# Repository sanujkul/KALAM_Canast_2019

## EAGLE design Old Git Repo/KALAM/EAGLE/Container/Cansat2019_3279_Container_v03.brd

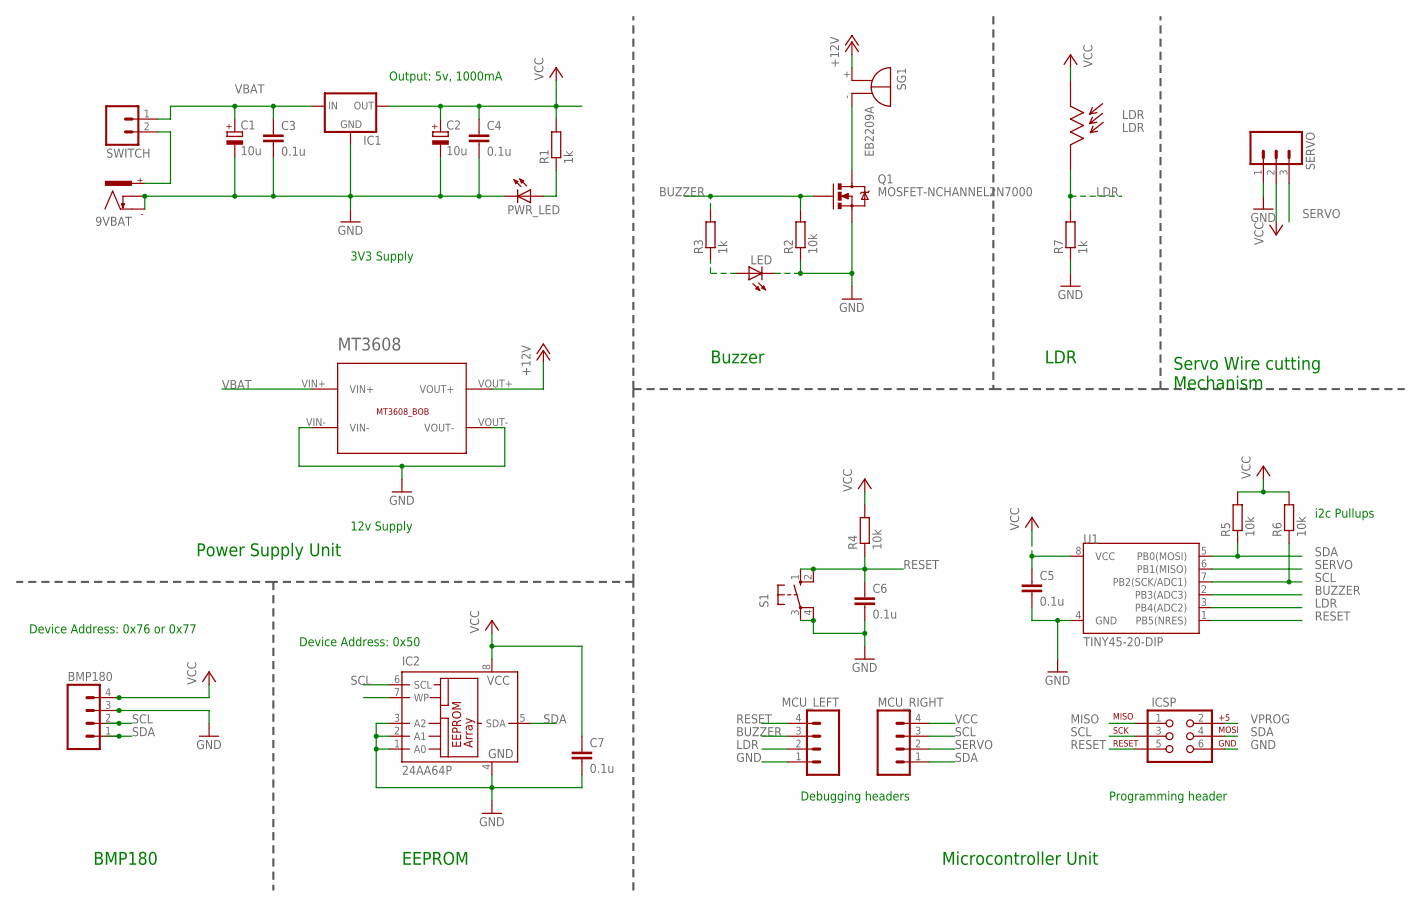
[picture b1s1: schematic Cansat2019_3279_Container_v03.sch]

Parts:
9VBAT: POWER_CON; NEB21R
BMP180: M04; 04P
C1, C2: 10u; E2,5-6
C3, C4, C5, C6, C7: 0.1u; C025-025X050
IC1: V_REG_78XX-TO-220; TO-220-ALT
IC2: 24AA64P; DIL8
ICSP: AVR_SPI_PRG_6NS; 2X3-NS
LDR: LDR; LDR-5MM
LED: LED3MM
MCU_LEFT: M04; 04P
MCU_RIGHT: M04; 04P
MT3608: MT3608_BOB
PWR_LED: LED3MM
Q1: MOSFET-NCHANNEL2N7000; TO-92
R1, R3, R7: 1k; 0204/7
R2, R4, R5, R6: 10k; 0204/7
S1: PUSH-BUTTON-6MM; B3F-10XX
SERVO: M03; 03P
SG1: EB2209A
SWITCH: M02; 02P
U1: TINY45-20-DIP; DIP08

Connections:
+12V: MT3608.VOUT+, SG1.+
BUZZER: MCU_LEFT.3, Q1.2 (G), R2.2, R3.2, U1.2 (PB3(ADC3))
GND: 9VBAT.-, 9VBAT.C, BMP180.3, C1.-, C2.-, C3.2, C4.2, C5.2, C6.2, C7.2, IC1.GND, IC2.1 (A0), IC2.2 (A1), IC2.3 (A2), IC2.4 (GND), ICSP.6, LED.K (C), MCU_LEFT.1, MT3608.VIN-, MT3608.VOUT-, PWR_LED.K (C), Q1.1 (S), R2.1, R7.1, S1.3, S1.4 (P1), SERVO.1, U1.4 (GND)
LDR: LDR.P$2, MCU_LEFT.2, R7.2, U1.3 (PB4(ADC2))
MISO: ICSP.1
unnamed: Q1.3 (D), SG1.-
unnamed: LED.A, R3.1
unnamed: PWR_LED.A, R1.1
unnamed: 9VBAT.+, SWITCH.2
RESET: C6.1, ICSP.5, MCU_LEFT.4, R4.1, S1.1 (S), S1.2 (S1), U1.1 (PB5(NRES))
SCL: BMP180.2, IC2.6 (SCL), ICSP.3, MCU_RIGHT.3, R6.1, U1.7 (PB2(SCK/ADC1))
SDA: BMP180.1, IC2.5 (SDA), ICSP.4, MCU_RIGHT.1, R5.1, U1.5 (PB0(MOSI))
SERVO: MCU_RIGHT.2, SERVO.3, U1.6 (PB1(MISO))
VBAT: C1.+, C3.1, IC1.IN, MT3608.VIN+, SWITCH.1
VCC: BMP180.4, C2.+, C4.1, C5.1, C7.1, IC1.OUT, IC2.8 (VCC), LDR.P$1, MCU_RIGHT.4, R1.2, R4.2, R5.2, R6.2, SERVO.2, U1.8 (VCC)
VPROG: ICSP.2

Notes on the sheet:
Power Supply Unit
Buzzer
Servo Wire cutting Mechanism
Debugging headers
Programming header
Microcontroller Unit
3V3 Supply
12v Supply
BMP180
i2c Pullups
Output: 5v, 1000mA
Device Address: 0x50
EEPROM
Device Address: 0x76 or 0x77
LDR

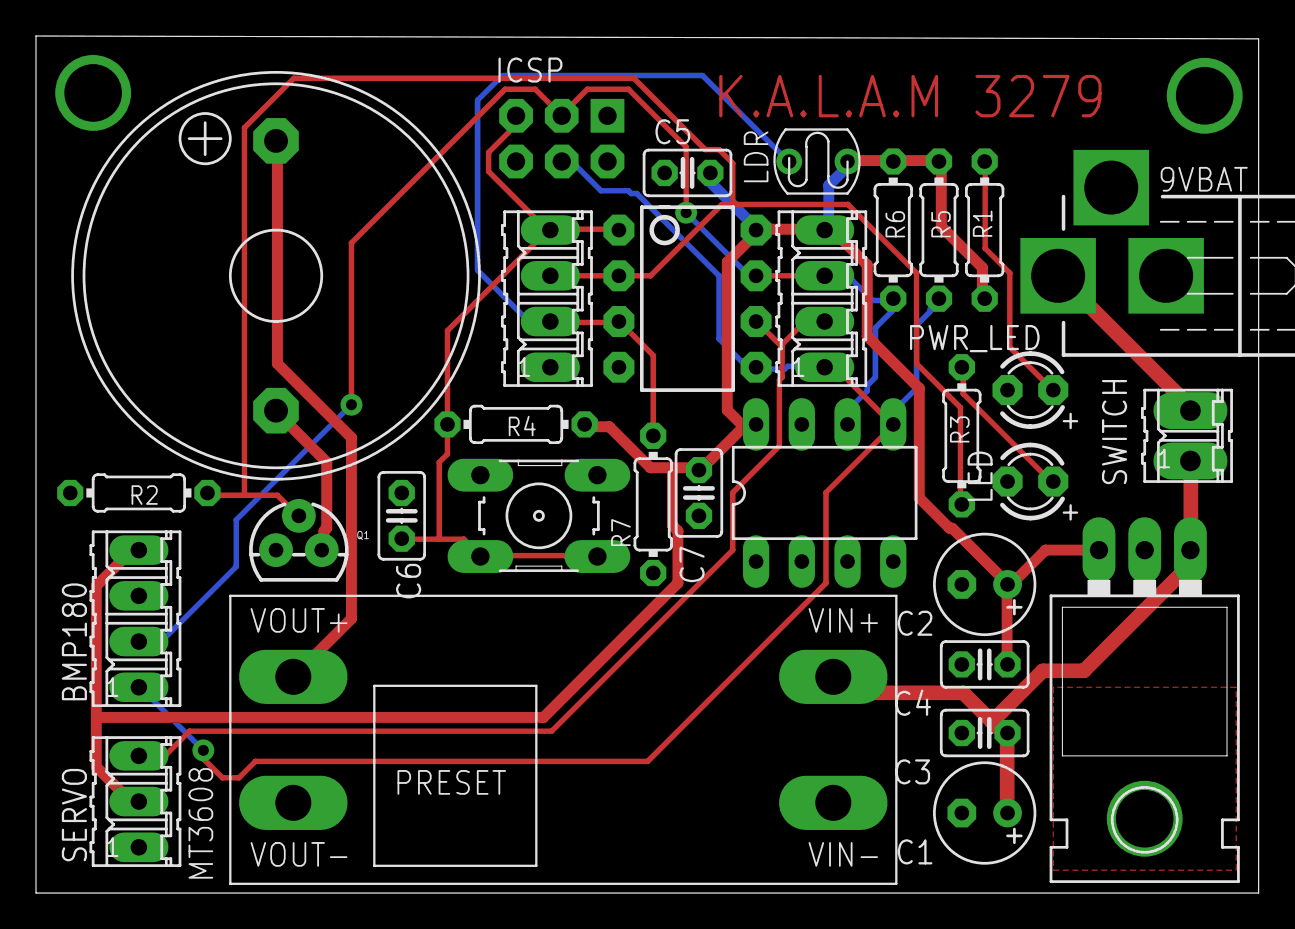
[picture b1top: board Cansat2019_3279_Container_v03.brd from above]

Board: 2 copper layers, 67.9 x 47.6 mm, 31 parts (0 on the bottom side), 14 nets.

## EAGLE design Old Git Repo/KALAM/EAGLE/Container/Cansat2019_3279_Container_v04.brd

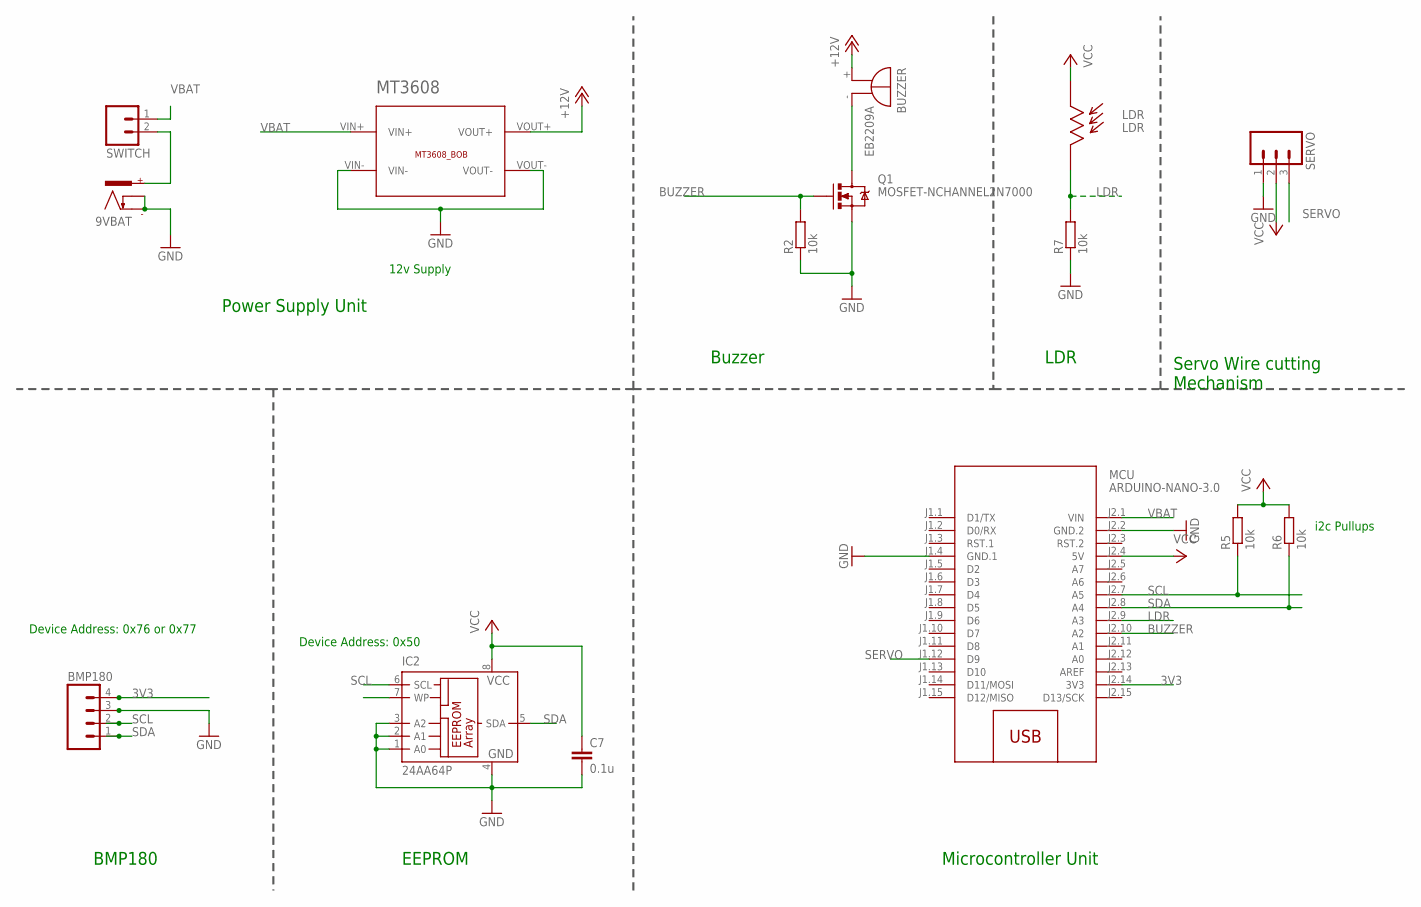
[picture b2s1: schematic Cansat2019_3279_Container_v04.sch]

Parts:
9VBAT: POWER_CON; NEB21R
BMP180: M04; 04P
BUZZER: EB2209A
C7: 0.1u; C025-025X050
IC2: 24AA64P; DIL8
LDR: LDR; LDR-5MM
MCU: ARDUINO-NANO-3.0
MT3608: MT3608_BOB
Q1: MOSFET-NCHANNEL2N7000; TO-92
R2, R5, R6, R7: 10k; 0204/7
SERVO: M03; 03P
SWITCH: M02; 02P

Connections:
3V3: BMP180.4, MCU.J2.14 (3V3)
+12V: BUZZER.+, MT3608.VOUT+
BUZZER: MCU.J2.10 (A2), Q1.2 (G), R2.2
GND: 9VBAT.-, 9VBAT.C, BMP180.3, C7.2, IC2.1 (A0), IC2.2 (A1), IC2.3 (A2), IC2.4 (GND), MCU.J1.4 (GND.1), MCU.J2.2 (GND.2), MT3608.VIN-, MT3608.VOUT-, Q1.1 (S), R2.1, R7.1, SERVO.1
LDR: LDR.P$2, MCU.J2.9 (A3), R7.2
unnamed: BUZZER.-, Q1.3 (D)
unnamed: 9VBAT.+, SWITCH.2
SCL: BMP180.2, IC2.6 (SCL), MCU.J2.7 (A5), R5.1
SDA: BMP180.1, IC2.5 (SDA), MCU.J2.8 (A4), R6.1
SERVO: MCU.J1.12 (D9), SERVO.3
VBAT: MCU.J2.1 (VIN), MT3608.VIN+, SWITCH.1
VCC: C7.1, IC2.8 (VCC), LDR.P$1, MCU.J2.4 (5V), R5.2, R6.2, SERVO.2

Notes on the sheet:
Power Supply Unit
Buzzer
Servo Wire cutting Mechanism
Microcontroller Unit
12v Supply
BMP180
i2c Pullups
Device Address: 0x50
EEPROM
Device Address: 0x76 or 0x77
LDR

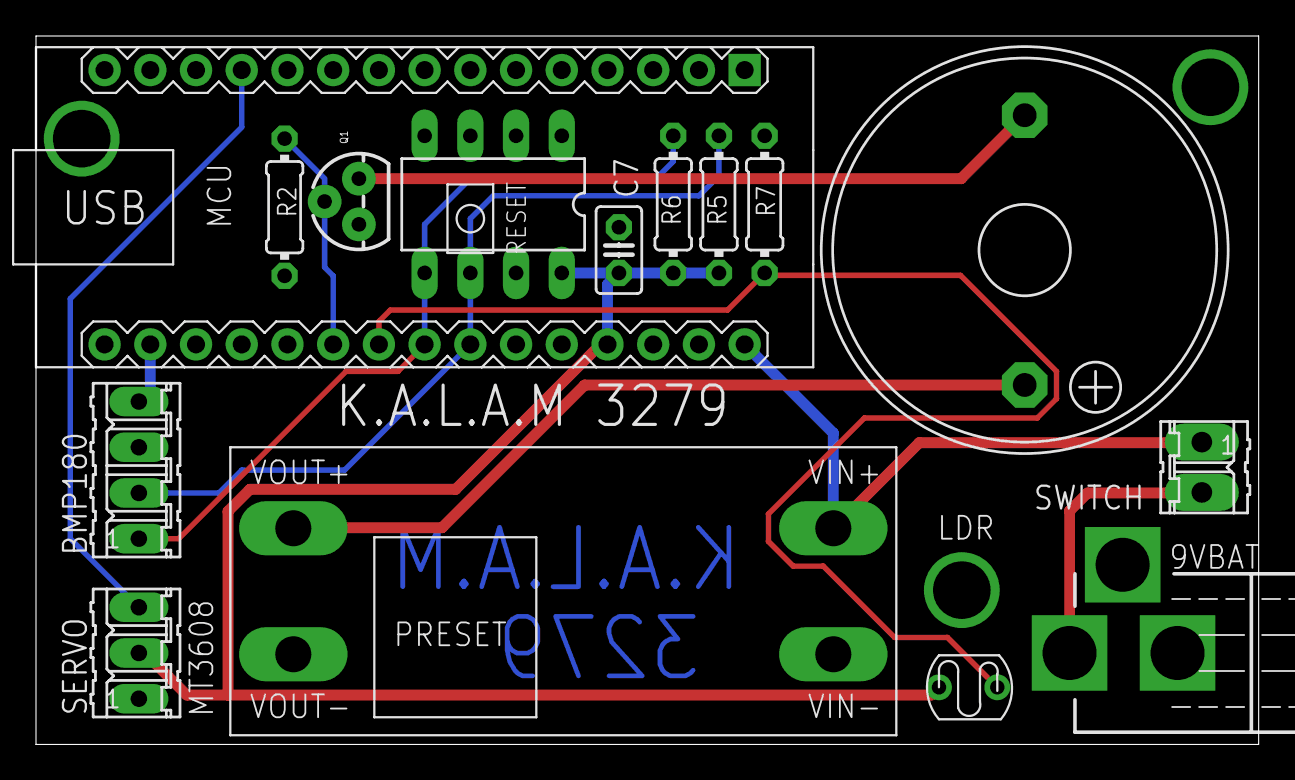
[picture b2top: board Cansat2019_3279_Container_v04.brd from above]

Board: 2 copper layers, 67.9 x 39.4 mm, 15 parts (0 on the bottom side), 12 nets.

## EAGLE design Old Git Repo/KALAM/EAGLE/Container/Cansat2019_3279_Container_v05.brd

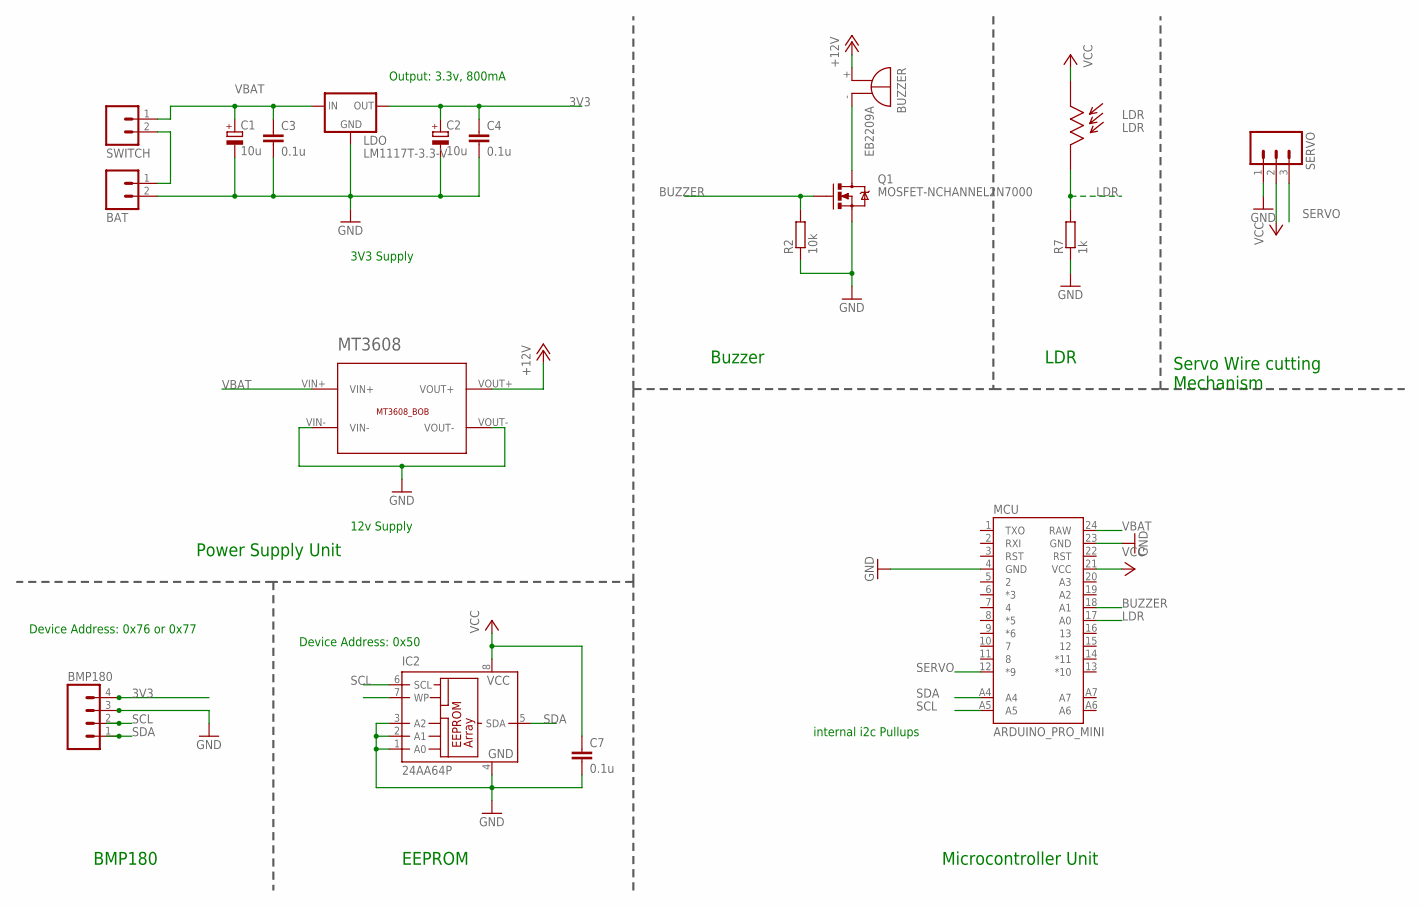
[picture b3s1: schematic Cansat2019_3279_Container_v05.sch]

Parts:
BAT: M02; 02P
BMP180: M04; 04P
BUZZER: EB2209A
C1, C2: 10u; E2,5-6
C3, C4, C7: 0.1u; C025-025X050
IC2: 24AA64P; DIL8
LDO: LM1117T-3.3-V; TO220V
LDR: LDR; LDR-5MM
MCU: ARDUINO_PRO_MINI
MT3608: MT3608_BOB
Q1: MOSFET-NCHANNEL2N7000; TO-92
R2: 10k; 0204/7
R7: 1k; 0204/7
SERVO: M03; 03P
SWITCH: M02; 02P

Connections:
3V3: BMP180.4, C2.+, C4.1, LDO.2 (OUT)
+12V: BUZZER.+, MT3608.VOUT+
BUZZER: MCU.18 (A1), Q1.2 (G), R2.2
GND: BAT.2, BMP180.3, C1.-, C2.-, C3.2, C4.2, C7.2, IC2.1 (A0), IC2.2 (A1), IC2.3 (A2), IC2.4 (GND), LDO.1 (GND), MCU.4 (GND), MCU.23 (GND), MT3608.VIN-, MT3608.VOUT-, Q1.1 (S), R2.1, R7.1, SERVO.1
LDR: LDR.P$2, MCU.17 (A0), R7.2
unnamed: BUZZER.-, Q1.3 (D)
unnamed: BAT.1, SWITCH.2
SCL: BMP180.2, IC2.6 (SCL), MCU.A5
SDA: BMP180.1, IC2.5 (SDA), MCU.A4
SERVO: MCU.12 (*9), SERVO.3
VBAT: C1.+, C3.1, LDO.3 (IN), MCU.24 (RAW), MT3608.VIN+, SWITCH.1
VCC: C7.1, IC2.8 (VCC), LDR.P$1, MCU.21 (VCC), SERVO.2

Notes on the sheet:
Power Supply Unit
Buzzer
Servo Wire cutting Mechanism
Microcontroller Unit
3V3 Supply
12v Supply
BMP180
Output: 3.3v, 800mA
Device Address: 0x50
EEPROM
Device Address: 0x76 or 0x77
LDR
internal i2c Pullups

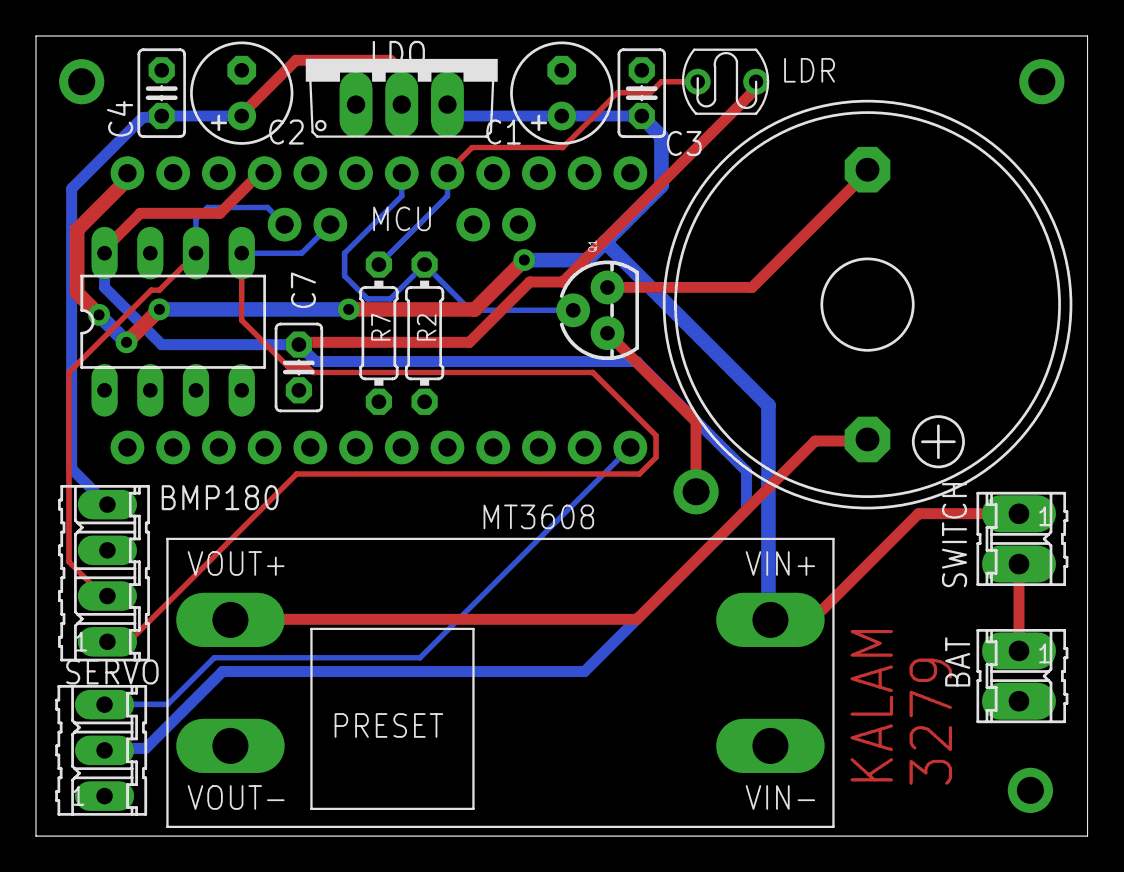
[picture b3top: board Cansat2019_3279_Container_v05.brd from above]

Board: 2 copper layers, 58.4 x 44.5 mm, 18 parts (0 on the bottom side), 12 nets.

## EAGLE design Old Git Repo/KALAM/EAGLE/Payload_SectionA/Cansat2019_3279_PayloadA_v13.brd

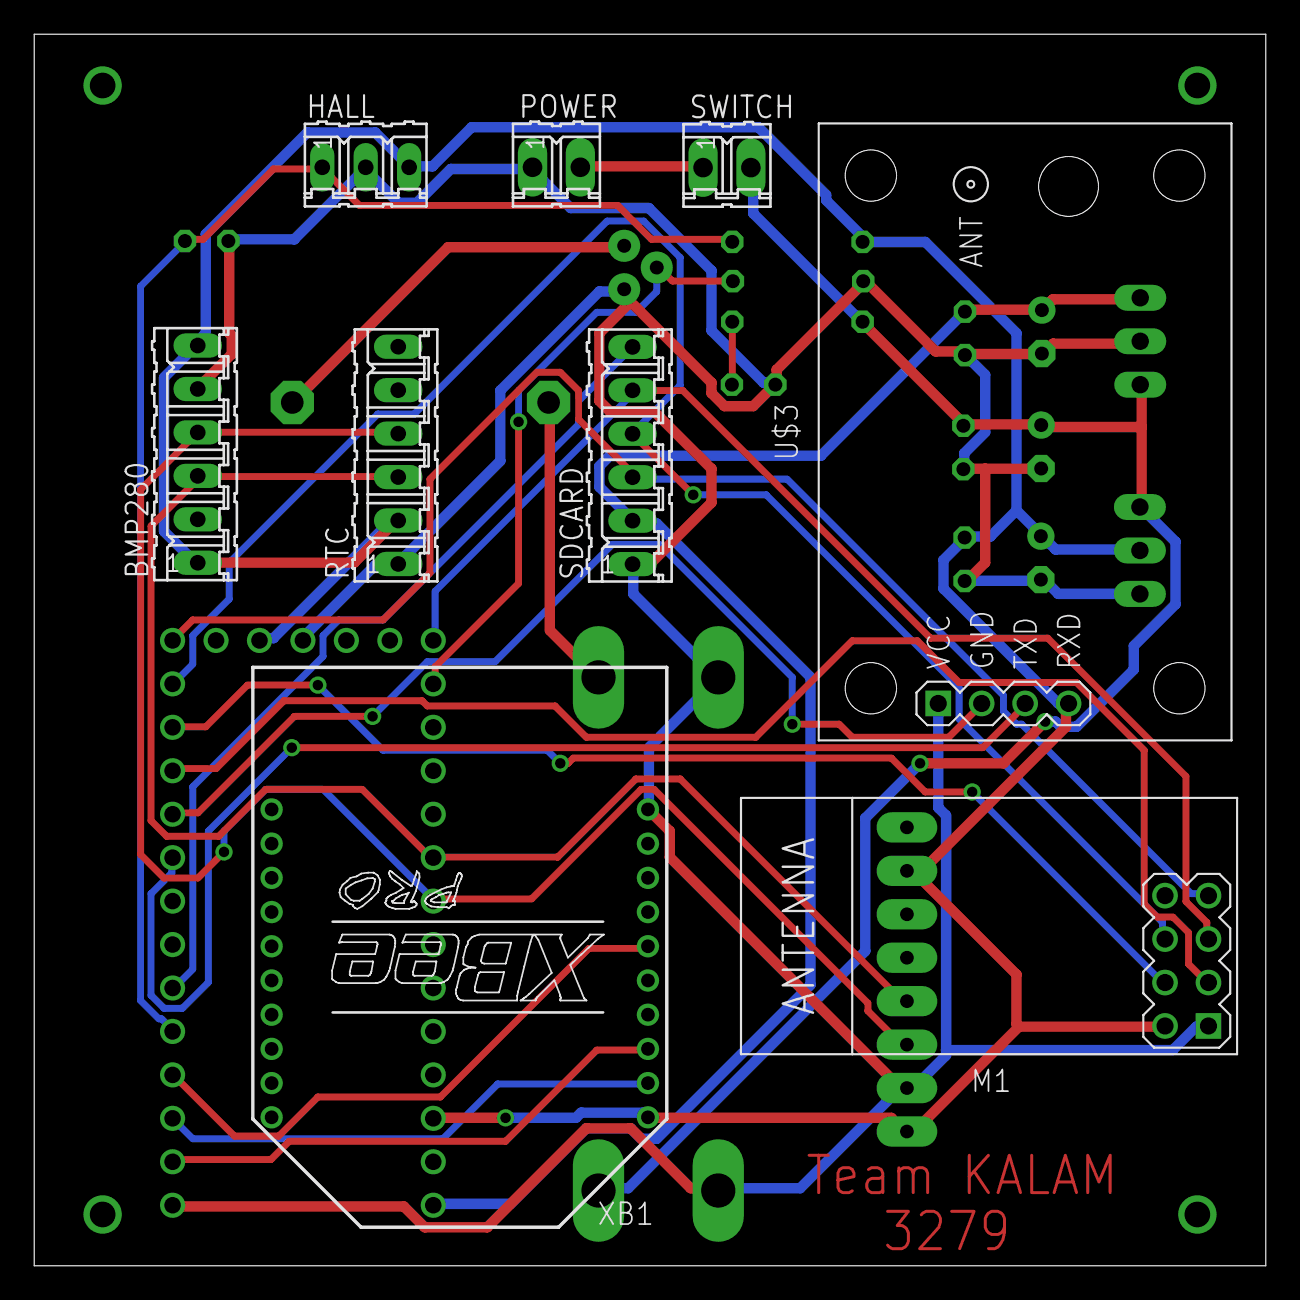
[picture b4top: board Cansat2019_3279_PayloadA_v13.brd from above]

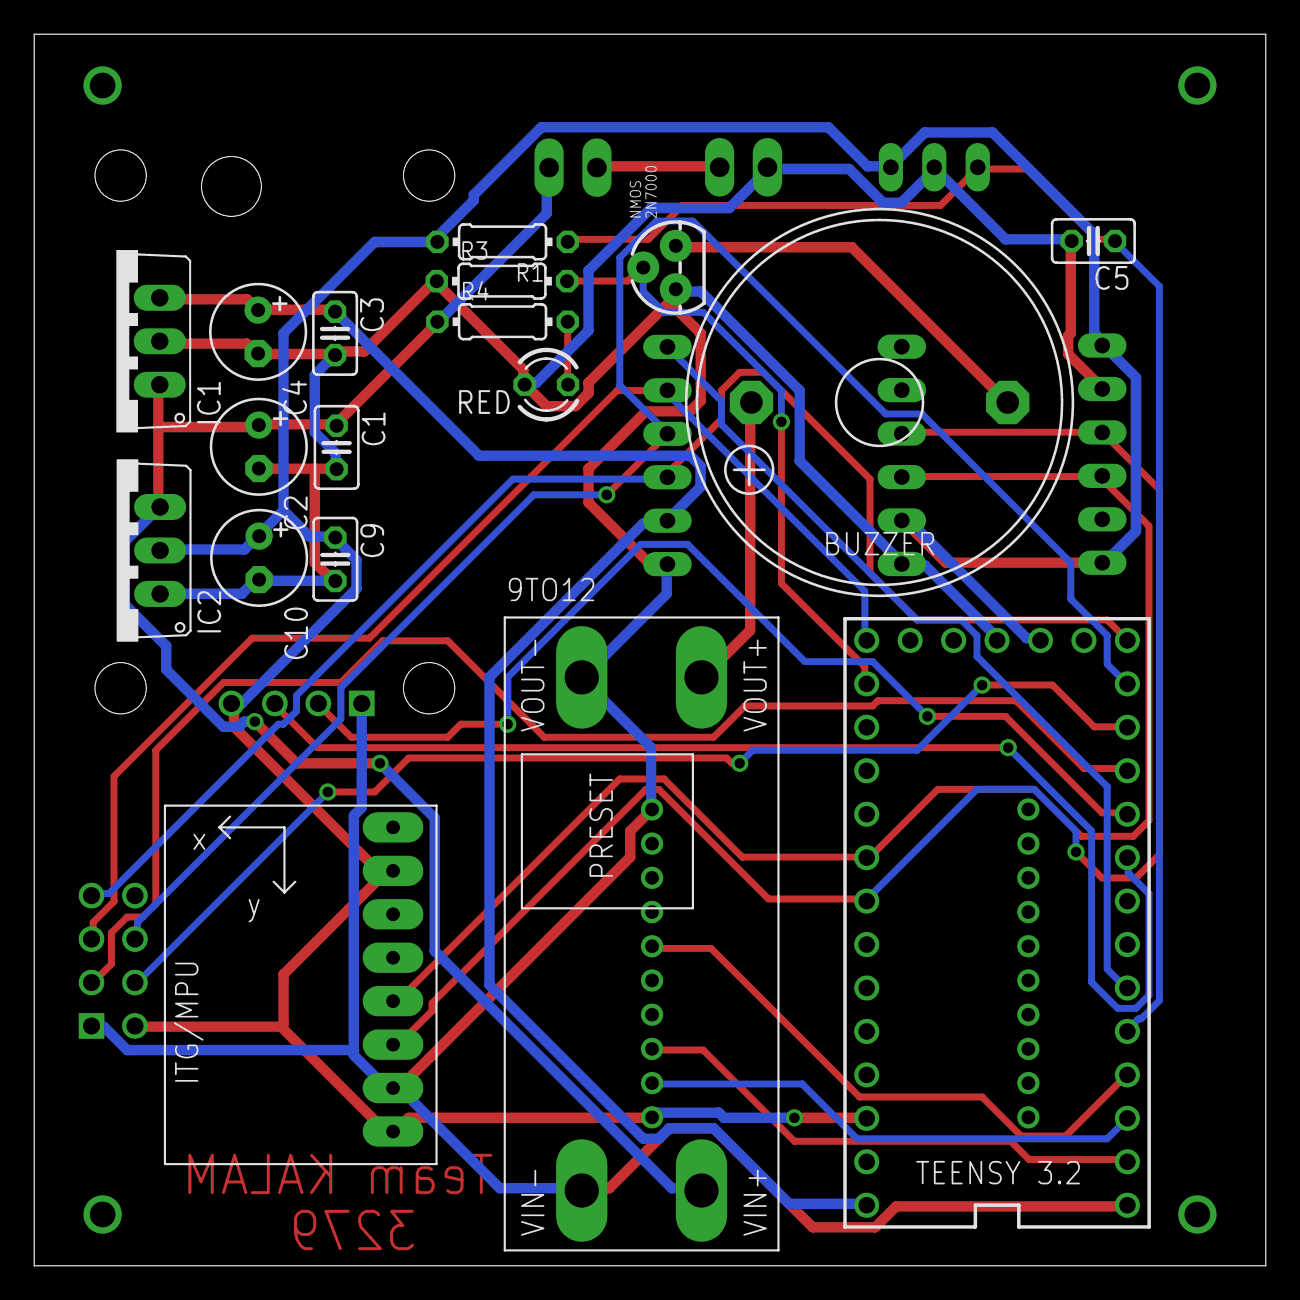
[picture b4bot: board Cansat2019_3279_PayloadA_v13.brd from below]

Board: 2 copper layers, 72.0 x 72.0 mm, 27 parts (18 on the bottom side), 23 nets.

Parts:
9TO12: BREAKOUTS_MT3608_BOB
BMP280: 06P
C1, C5, C9: 0.1u; C025-025X050
C2, C10: 10u; E2,5-6
C3: 10u; C025-025X050
C4: 0.1u; E2,5-6
HALL: 03P
IC1: 7805TV; TO220V
IC2: LM1117T-3.3-V; TO220V
M1: WIRELESS-NRF24L01
POWER: CEDT_JANUARY_2015_V5_02P
Q1: SPARKFUN-DISCRETESEMI_MOSFET-NCHANNEL2N7000; SPARKFUN-DISCRETESEMI_TO-92
R1: 10k; 0204/7
R3: 1K; 0204/7
R4: 1k; 0204/7
RED: red; LED3MM
RTC: 06P
SDCARD: 06P
SG1: BUZZER_EB2209A
SWITCH: 02P
U1: GY-521MPU6050; GY-521
U$2: TEENSY_3.1-3.2_OUTER_ROW; TEENSY_3.0-3.2&LC_OUTER_ROW
U$3: GPS-RECEIVER-NEO6M
XB1: XBEE-PRO

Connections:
3.3V: BMP280.1, BMP280.6, C9.1, C10.+, HALL.3, IC2.2, M1.2, R1.2, RTC.2, U1.ADO, U1.VCC, U$2.3.3V, U$2.3.3V1, U$3.4, XB1.1
5V: C3.1, C4.+, IC1.3, SDCARD.2, U$2.VIN
9V: 9TO12.VIN+, C1.1, C2.+, IC1.1, IC2.3, R4.1, SWITCH.2
12V: 9TO12.VOUT+, SG1.+
BUZZER: Q1.2, R3.2, U$2.14/A0
CSNNRF: M1.4, U$2.10
CSNRF: M1.3, U$2.9
CSSDCARD: SDCARD.6, U$2.4
GND: 9TO12.VIN-, 9TO12.VOUT-, BMP280.5, C1.2, C2.-, C3.2, C4.-, C5.2, C9.2, C10.-, HALL.2, IC1.2, IC2.1, M1.1, POWER.1, Q1.1, R3.1, RED.K, RTC.1, SDCARD.1, U1.GND, U$2.GND, U$2.GND1, U$3.1, XB1.10
HALLIP: C5.1, HALL.1, R1.1, U$2.3
MISO: M1.7, SDCARD.3, U$2.12
MOSI: M1.6, SDCARD.4, U$2.11
unnamed: POWER.2, SWITCH.1
unnamed: R4.2, RED.A
unnamed: Q1.3, SG1.-
RSSI: U$2.2, XB1.6
RXBEE: U$2.1, XB1.2
RXGPS: U$2.8, U$3.2
SCK: M1.5, SDCARD.5, U$2.13
SCL: BMP280.4, RTC.4, U1.SCL, U$2.19/A5
SDA: BMP280.3, RTC.3, U1.SDA, U$2.18/A4
TXBEE: U$2.0, XB1.3
TXGPS: U$2.7, U$3.3

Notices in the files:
parts and their libraries:
SparkFun-Connectors: Licensing: Creative Commons ShareAlike 4.0 International - https://creativecommons.org/licenses/by-sa/4.0
diy-modules: Released under the Creative Commons Attribution 4.0 International License: http://creativecommons.org/licenses/by/4.0
